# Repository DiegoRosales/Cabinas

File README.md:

Proyecto Cabinas
=======
---

**Última revisión del PCB del control:** 09/09/2014.

**Última revisión del PCB de la botonera:** 29/07/2014.

**Última revisión del código del control:** 23/09/2014.

**Última revisión del código de la botonera:** 1/09/2014

# Esquemático del PCB de control

# Esquemático de la botonera

# Tabla de cableado

# BOM
[Bill of materials](https://github.com/DiegoRosales/Cabinas/blob/master/PCB/Cabinas/BOM/BOM.xlsx)

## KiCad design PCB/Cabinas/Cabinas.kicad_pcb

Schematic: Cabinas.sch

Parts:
A1, A2: PROMINI
C1: 0.33uF
C2, C4, C5, C6: 0.1uF
C3, C8, C14: 10uF
C7, C13: 470uF
C12: 10pF
D1, D2, D3, D4, D5, D6, D13, D14, D15, D16, D17, D18, D25: DIODE
D7, D8, D9, D10, D11, D12, D19, D20, D21, D22, D23, D24: LED
FB1: FILTER
J1, J2: JACK_ST
JP2: JUMPER
K1, K2: CONN_3
MP31: VS1053_ADAFRUIT
P1, P2, P3, P4, P5, P6, P7, P8: CONN_4
P9, P10, P11: CONN_2
P13: DIN_5
Q1, Q2, Q3, Q4, Q5, Q6, Q7, Q8, Q9, Q10, Q11, Q12: MOSFET_N
R1, R2, R3, R4, R5, R6, R7, R8, R9, R10, R11, R12, R15, R16, R17: 1k
R13, R14: 4.7k
R18: 0R
R19: 100
R21, R22, R29, R30: R
R24, R25, R26, R27, R28: 10k
RV1, RV2, RV3: 10k
SW1, SW2, SW3, SW4, SW5, SW6, SW7, SW8, SW9, SW10, SW11, SW12, SW13, SW14, SW15: PUSHBUTTON
TP2: CONN_2
U1: BTM_2
U2: 7805
U3: LM386
U4, U5: 74HC595
U6: TL082

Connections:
1: SW1.2, U4.15 (QA)
2: SW2.2, U4.1 (QB)
3: SW3.2, U4.2 (QC)
4: SW4.2, U4.3 (QD)
5: SW5.2, U4.4 (QE)
6: SW6.2, U4.5 (QF)
7: SW7.2, U4.6 (QG)
8: SW8.2, U4.7 (QH)
9: SW9.2, U5.15 (QA)
10: SW10.2, U5.1 (QB)
11: SW11.2, U5.2 (QC)
12: SW12.2, U5.3 (QD)
+5V: A1.25 (Vcc), A2.25 (Vcc), C4.1, C5.1, C13.1, FB1.1, JP2.1, MP31.26 (VCC), P13.4, R13.1, R14.1, R26.1, R27.1, R28.1, SW1.3, SW1.4, SW2.3, SW2.4, SW3.3, SW3.4, SW4.3, SW4.4, SW5.3, SW5.4, SW6.3, SW6.4, SW7.3, SW7.4, SW8.3, SW8.4, SW9.3, SW9.4, SW10.3, SW10.4, SW11.3, SW11.4, SW12.3, SW12.4, TP2.1, U4.10 (SRCLR), U4.16 (VCC), U5.10 (SRCLR), U5.16 (VCC); also elsewhere on the board
+12P: C1.1, D25.2 (K), P10.2 (PM), R24.2, U2.VI, U2.Vi, U6.8 (V+); also elsewhere on the board
+12V: C6.1, C7.1, D1.2 (K), D2.2 (K), D3.2 (K), D4.2 (K), D5.2 (K), D6.2 (K), D13.2 (K), D14.2 (K), D15.2 (K), D16.2 (K), D17.2 (K), D18.2 (K), P1.4, P2.4, P3.4, P4.4, P5.4, P6.4, P7.4, P8.4, P9.2 (PM), U3.6 (Pwr)
A0 (RX): A1.21 (A0), U1.3 (TX)
A1 (TX): A1.22 (A1), R15.2, R17.1
GND: A1.4 (Gnd), A1.27 (GND), A2.4 (Gnd), A2.27 (GND), C1.2, C2.2, C3.2, C4.2, C5.2, C6.2, C7.2, C13.2, D7.2 (K), D8.2 (K), D9.2 (K), D10.2 (K), D11.2 (K), D12.2 (K), D19.2 (K), D20.2 (K), D21.2 (K), D22.2 (K), D23.2 (K), D24.2 (K), J1.1, J1.2, J2.1, K1.1, K2.1, MP31.30 (AGND), P9.1, P10.1, P11.1, P13.5, Q1.S, Q2.S, Q3.S, Q4.S, Q5.S, Q6.S, Q7.S, Q8.S, Q9.S, Q10.S, Q11.S, Q12.S, R16.1, R19.1, R25.1, RV1.3, SW13.1, SW13.2, SW14.1, SW14.2, SW15.1, SW15.2, TP2.2 (PM), U1.4 (GND), U2.GND, U3.2 (-), U3.4 (Gnd), U4.8 (GND), U5.8 (GND), U6.4 (V-); also elsewhere on the board
I2CSCL: A1.30 (A5), A2.30 (A5), K2.3, P13.2, R14.2
I2CSDA: A1.29 (A4), A2.29 (A4), K2.2 (PM), P13.1, R13.2
LOUT: K1.2 (PM), MP31.31 (LOUT), R29.1
MIC_PREAMP: C8.2, P11.2 (PM), R22.1, R30.1
MP3_RESET: A2.8 (D5), R28.2, SW15.3, SW15.4
unnamed: D16.1 (A), P7.1, P8.1, Q10.D
unnamed: Q10.G, R10.2, SW10.1
unnamed: D21.1 (A), R9.1
unnamed: Q9.G, R9.2, SW9.1
unnamed: D17.1 (A), P7.2, P8.2, Q11.D
unnamed: D23.1 (A), R11.1
unnamed: Q11.G, R11.2, SW11.1
unnamed: D22.1 (A), R10.1
unnamed: D14.1 (A), P5.2, P6.2, Q8.D
unnamed: D19.1 (A), R7.1
unnamed: Q7.G, R7.2, SW7.1
unnamed: D15.1 (A), P5.3, P6.3, Q9.D
unnamed: D20.1 (A), R8.1
unnamed: Q8.G, R8.2, SW8.1
unnamed: C2.1, D25.1 (A), JP2.2 (PM), U2.VO, U2.Vo
unnamed: U4.9 (~QH), U5.14 (SER)
unnamed: D24.1 (A), R12.1
unnamed: Q12.G, R12.2, SW12.1
unnamed: D18.1 (A), P7.3, P8.3, Q12.D
unnamed: R15.1, R16.2, R17.2, U1.2 (RX)
unnamed: D7.1 (A), R1.1
unnamed: Q1.G, R1.2, SW1.1
unnamed: D1.1 (A), P1.1, P2.1, Q1.D
unnamed: D8.1 (A), R2.1
unnamed: Q2.G, R2.2, SW2.1
unnamed: D2.1 (A), P1.2, P2.2, Q2.D
unnamed: R29.2, R30.2, RV3.3, U6.6 (-)
unnamed: R21.2, R22.2, RV2.3, U6.2 (-)
unnamed: D11.1 (A), R5.1
unnamed: D6.1 (A), P3.3, P4.3, Q6.D
unnamed: Q5.G, R5.2, SW5.1
unnamed: D12.1 (A), R6.1
unnamed: D13.1 (A), P5.1, P6.1, Q7.D
unnamed: Q6.G, R6.2, SW6.1
unnamed: D9.1 (A), R3.1
unnamed: Q3.G, R3.2, SW3.1
unnamed: D4.1 (A), P3.1, P4.1, Q4.D
unnamed: D3.1 (A), P1.3, P2.3, Q3.D
unnamed: Q4.G, R4.2, SW4.1
unnamed: D10.1 (A), R4.1
unnamed: A2.17 (D10), MP31.19 (CS)
unnamed: A2.12 (D9), MP31.20 (RST)
unnamed: A2.11 (D8), MP31.17 (XDCS)
unnamed: A2.7 (D4), MP31.18 (SDCS)
unnamed: A2.6 (D3), MP31.27 (DREQ)
unnamed: J2.3, RV2.1, RV2.2, U6.1
unnamed: A2.19 (D12), MP31.23 (MISO)
unnamed: A2.18 (D11), MP31.22 (MOSI)
unnamed: A2.20 (D13), MP31.21 (SCLK)
unnamed: R18.2, U3.8 (Gain)
unnamed: C14.2, R18.1
unnamed: C8.1, C12.2, U3.5
unnamed: C12.1, R19.2
unnamed: C3.1, U3.7 (Bypass)
unnamed: J2.2, RV3.1, RV3.2, U6.7
unnamed: RV1.2, U3.3 (+)
unnamed: J1.3, RV1.1
unnamed: D5.1 (A), P3.2, P4.2, Q5.D
unnamed: C14.1, U3.1 (Gain)
unnamed: FB1.2, U1.5 (Vcc)
Next: A2.9 (D6), R27.2, SW14.3, SW14.4
Play: A2.10 (D7), R26.2, SW13.3, SW13.4
ROUT: K1.3, MP31.32 (ROUT), R21.1
SR_CLK: A1.12 (D9), U4.11 (SRCLK), U5.11 (SRCLK)
SR_Input: A1.9 (D6), U4.14 (SER)
SR_LCLK: A1.11 (D8), U4.12 (RCLK), U5.12 (RCLK)
SR_OE: A1.10 (D7), U4.13 (G), U5.13 (G)
Vbias: R24.1, R25.2, U6.3 (+), U6.5 (+)

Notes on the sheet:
Arduino - TX BTM - RX
Arduino - RX BTM - TX
Bluetooth Module
MP3 Module
I2C and Button pad Power Supply
5V Regulator
Arduino Pro Mini
Decoupling
LED Output
LED PSU
Shift register
Grupo A/G
Grupo B/H
Grupo C/D
Grupo F/I
Digital PSU
Test Points
Mixer
Mic Preamp
Virtual GND
Power
Audio
I2C

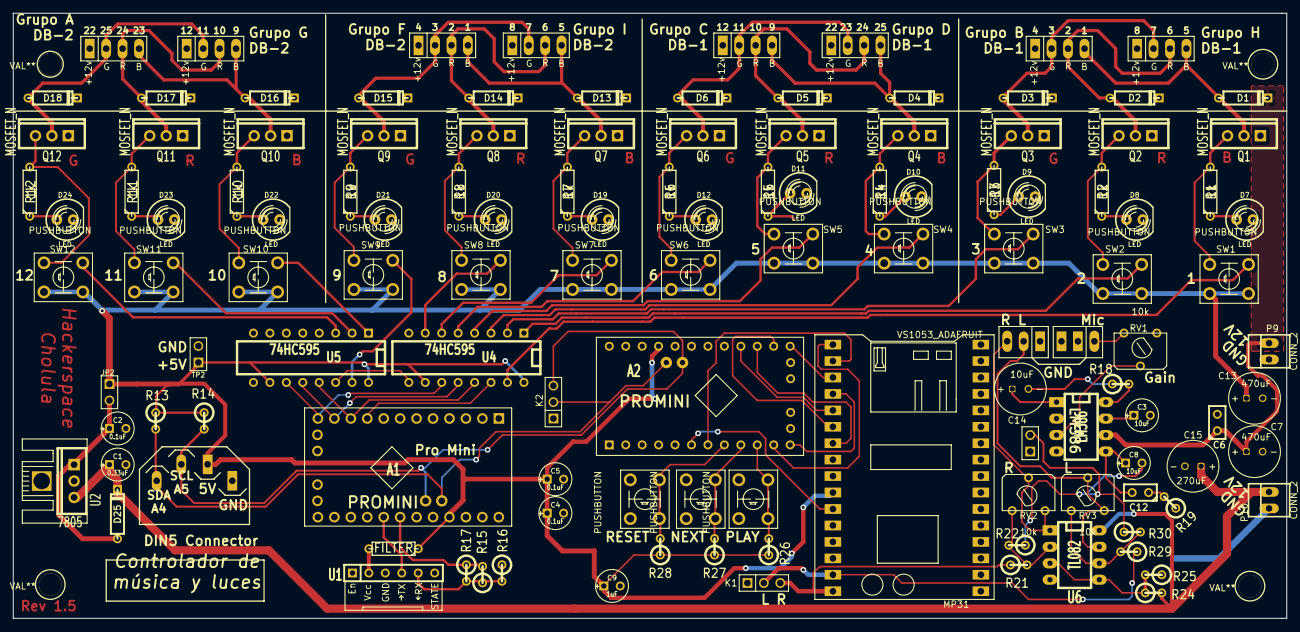
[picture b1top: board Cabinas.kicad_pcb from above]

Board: 2 copper layers, 196.7 x 93.5 mm, 128 parts (0 on the bottom side), 91 nets.

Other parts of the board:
3.5mm_Screw, 3.5mm_Screw#2, 3.5mm_Screw#3, 3.5mm_Screw#4: VAL**; 3.5mm_Screw
C9: 1uF; C1V5
C15: 270uF; CAP_8_3.5

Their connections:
+5V: C9.1; also elsewhere on the board
+12P: C15.1; also elsewhere on the board
GND: C9.2, C15.2; also elsewhere on the board

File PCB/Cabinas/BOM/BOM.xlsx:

| Reference | Value | Type
 | A1 | - | Arduino Pro Mini 5V
 | C1 | 0.33uF | Ceramic Capacitor
 | C9, C10, C11, C12 | 1uF | Electrolytic Capacitor
 | C7, C13 | 470uF | Electrolytic Capacitor
 | C2, C3, C4, C5, C6 | 0.1uF | Ceramic Capacitor
 | C8 | 47uF | Electrolytic Capacitor
 | D7, D8, D9, D10, D11, D12, D19, D20, D21, D22, D23, D24 | LED | LED
 | D1, D2, D3, D4, D5, D6D13, D14, D15, D16, D17, D18 | 1N4001 | Diode
 | ELEC1 | - | Electret Microphone
 | GS1 | - | Solder jumper
 | GS2 | - | Solder jumper
 | J1 | JACK_ST_3SW | Jack
 | JP1, JP2 | - | Pin header 2x
 | K1 | - | Pin header 3x
 | M1 | WTV020-SD | MP3 Module
 | P1, P2, P3, P4, P5, P6, P7, P8 | - | LED Strip output
 | P13 | - | DIN 5 Connector
 | Q1, Q2, Q3, Q4, Q5, Q6, Q7, Q8, Q9, Q10, Q11, Q12 |  | Mosfet transistor
 | R1, R2, R3, R4, R5, R6, R7, R8, R9, R10, R11, R12, R15, R16, R17 | 1k | Resistor
 | R13, R14 | 4.7k | Resistor
 | R18, R19, R21, R22, R23, R24, R26 | 10k | Resistor
 | R20 | 270k | Resistor
 | R25 | 2.2k | Resistor
 | REG1 | NPC1700 | 3.3V Regulator
 | SW1, SW2, SW3, SW4, SW5, SW6, SW7, SW8, SW9, SW10, SW11, SW12 | - | Tactile Switch
 | U1 | - | Bluetooth module
 | U2 | 7805 | 5V Regulator
 | U3 | TL072 | Operational Amplifier
 | U4, U5 | 74HC595 | Shift Register

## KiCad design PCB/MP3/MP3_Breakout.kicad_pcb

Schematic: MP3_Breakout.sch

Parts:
K1: CONN_3
MCU1: PRO_MINI_2
MP31: VS1053_ADAFRUIT
P1, P2: CONN_2

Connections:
+5V: MCU1.25, MP31.26 (VCC), P1.1
/A4_SDA: MCU1.14, P2.1
/A5_SCL: MCU1.13, P2.2 (PM)
GND: K1.3, MCU1.27, MP31.24 (GND), P1.2 (PM)
unnamed: K1.1, MP31.31 (LOUT)
unnamed: MCU1.20, MP31.21 (SCLK)
unnamed: MCU1.6, MP31.27 (DREQ)
unnamed: K1.2 (PM), MP31.32 (ROUT)
unnamed: MCU1.12, MP31.20 (RST)
unnamed: MCU1.17, MP31.19 (CS)
unnamed: MCU1.19, MP31.23 (MISO)
unnamed: MCU1.7, MP31.18 (SDCS)
unnamed: MCU1.11, MP31.17 (XDCS)
unnamed: MCU1.18, MP31.22 (MOSI)

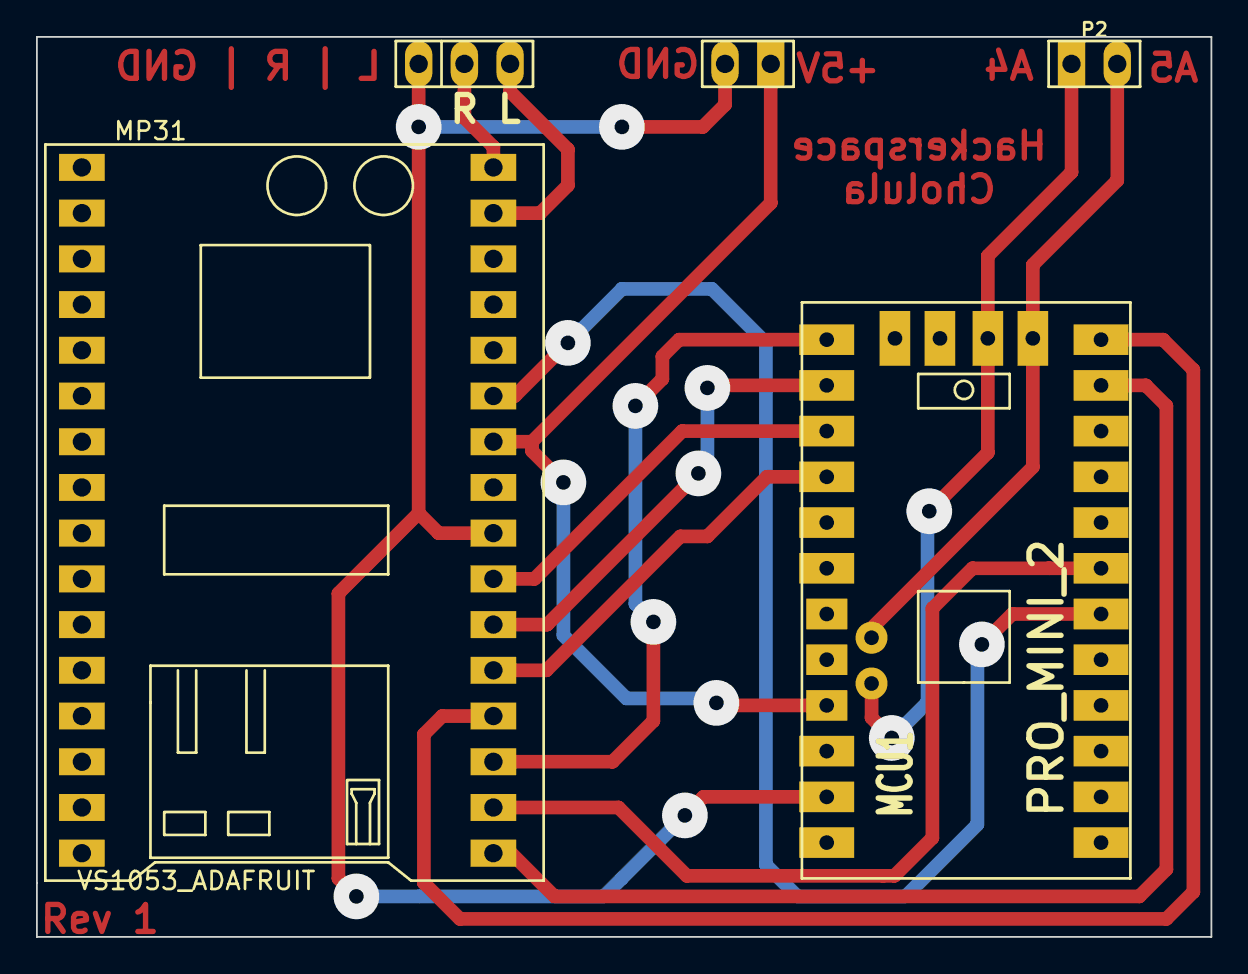
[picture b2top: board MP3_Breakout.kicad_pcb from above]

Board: 2 copper layers, 65.2 x 50.0 mm, 5 parts (0 on the bottom side), 14 nets.

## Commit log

2014-08-04 Rev 1.2
    Rev 1.2
2014-08-04 BOM
    BOM
2014-08-04 Create README.md
    Readme
2014-08-08 Codigo
    Codigo
2014-08-08 Prueba MP3
    Prueba MP3
2014-08-19 mySerial
    9600 baud
2014-09-04 Librerias actualizadas
2014-09-04 Mejora de codigo
2014-09-11 PCB Rev 1.3
2014-09-15 Actualizacion de codigo
2014-09-18 stackdump
2014-09-18 Menos ruido
2014-09-23 Cambios
    *, #
    Optimizacion de memoria
    Aumento de tiempo de rutinas
2014-09-23 readme
2014-09-25 Apagado de protección
    Apagado de protección
    Eliminación de mensajes de depuración
2014-09-30 Cambios
    Los botones * y # ahora inician únicamente las canciones, no la rutina
    completa.
2014-09-30 Correcciones
    Correcciones de botonera
2014-09-30 Codigo de botonera
2014-10-14 Rev 1.4
2014-12-16 MP3 Breakout board
    MP3 Breakout board
2014-12-23 Codigo 2.1
2015-01-19 Actualizacion de codigo
    actualizacion de codigo para mp3 estereo
2015-01-21 Rev 1.5
    Audio estereo
2015-02-23 Firmware V3.0
2015-03-19 REV 1.5
    Codigo V3.0
2015-04-06 Rev 3.0.2
    Se aumento el tiempo de rutina a 16 minutos
2015-05-15 Revision
